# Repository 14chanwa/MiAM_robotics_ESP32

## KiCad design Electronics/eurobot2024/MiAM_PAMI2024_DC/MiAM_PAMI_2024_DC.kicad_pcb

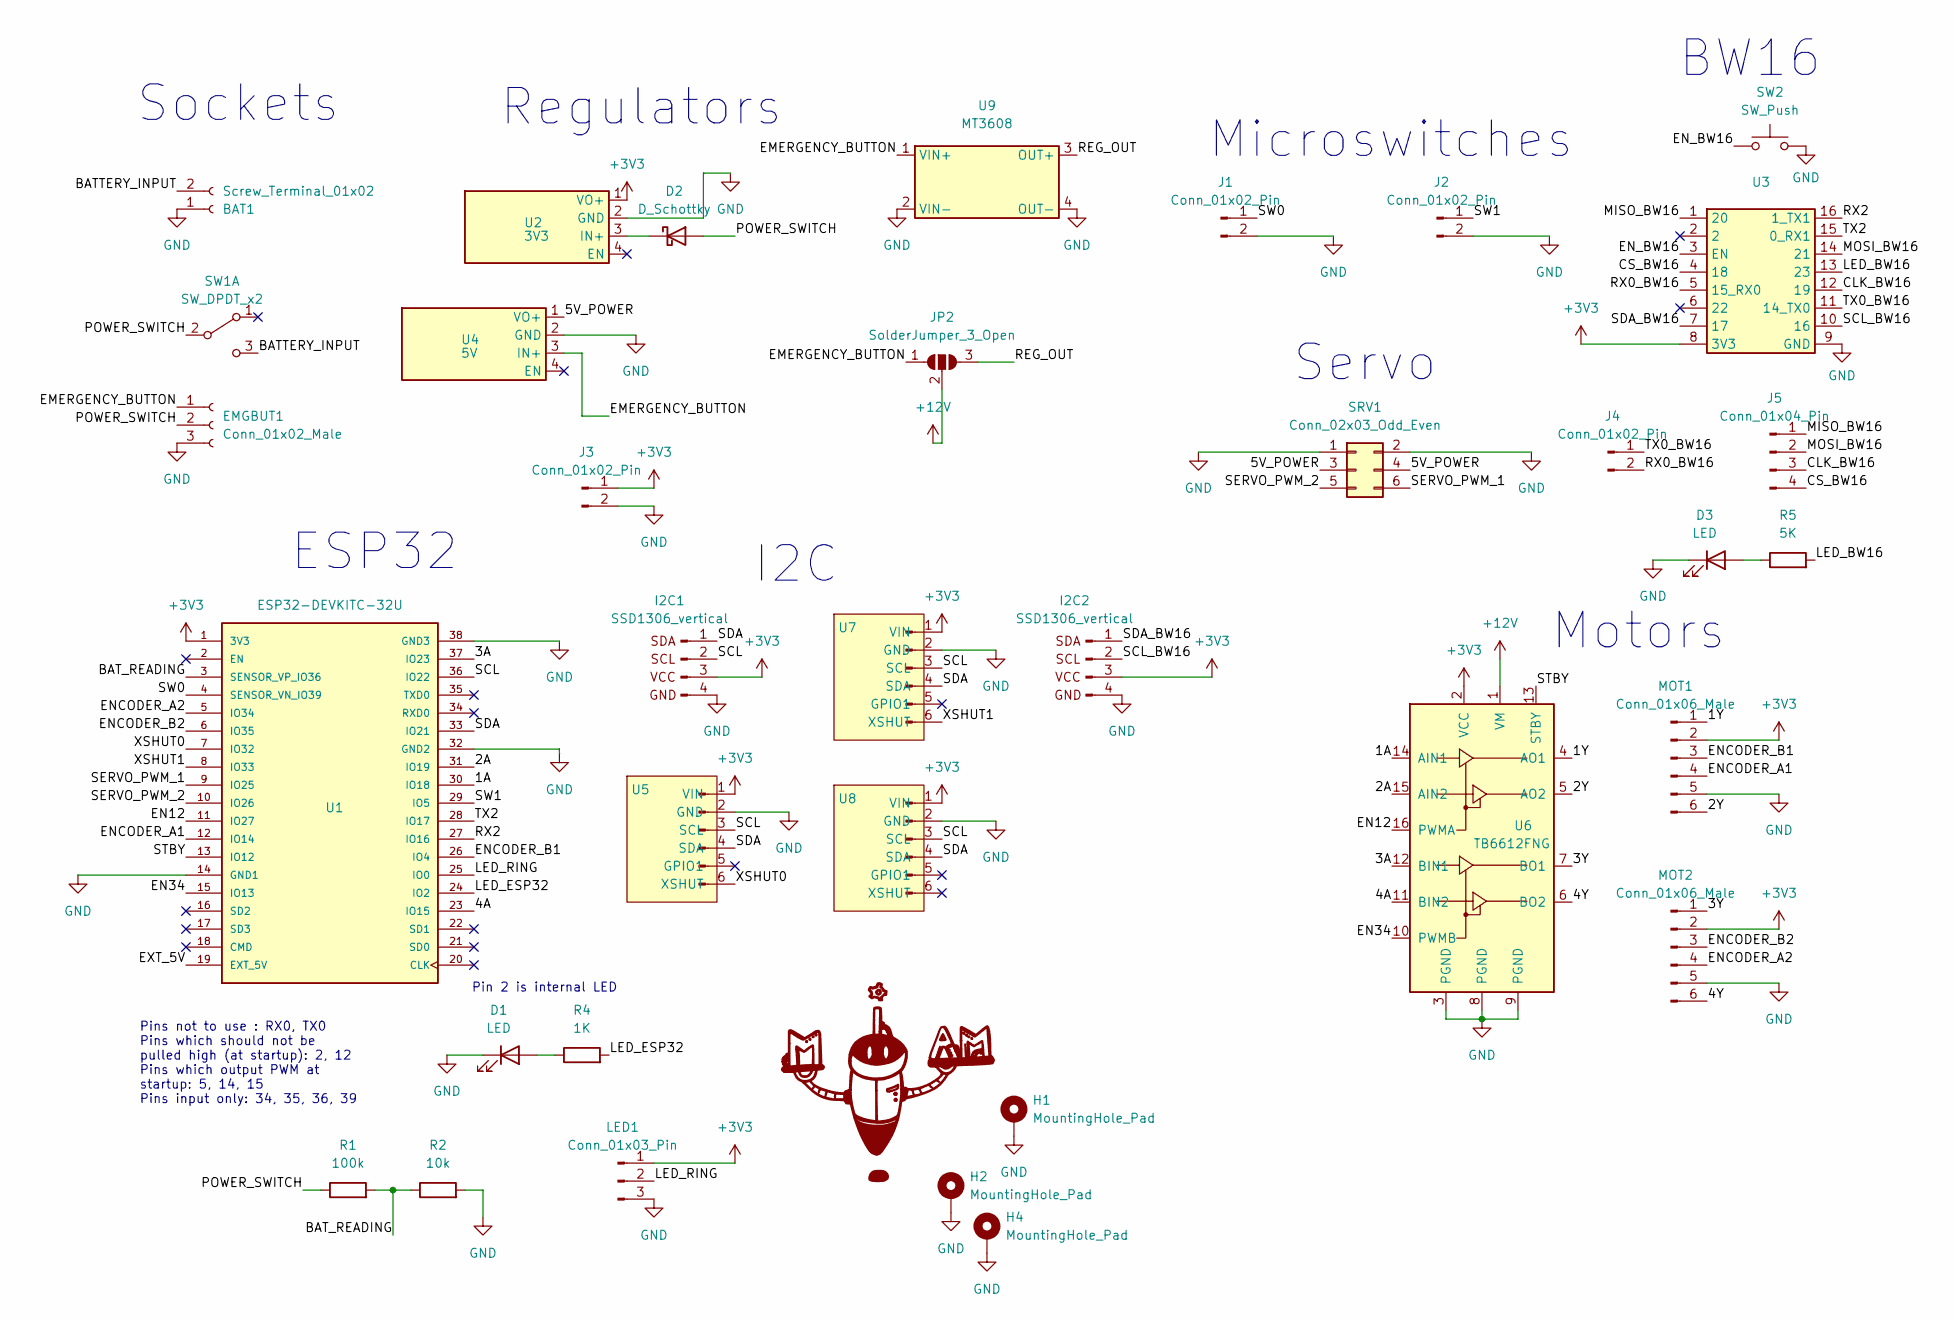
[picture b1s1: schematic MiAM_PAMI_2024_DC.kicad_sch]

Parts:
BAT1: Screw_Terminal_01x02; JST_PH_B2B-PH-K_1x02_P2.00mm_Vertical
D1, D3: LED; LED_0805_2012Metric
D2: D_Schottky; D_SOD-323_HandSoldering
EMGBUT1: Conn_01x02_Male; JST_PH_B3B-PH-K_1x03_P2.00mm_Vertical
H1, H2, H4: MountingHole_Pad; MountingHole_3.2mm_M3_DIN965_Pad
I2C1, I2C2: SSD1306_vertical; PinHeader_1x04_P2.54mm_Vertical
J1, J2, J3, J4: Conn_01x02_Pin; PinHeader_1x02_P2.54mm_Vertical
J5: Conn_01x04_Pin; PinHeader_1x04_P2.54mm_Vertical
JP2: SolderJumper_3_Open; SolderJumper-3_P1.3mm_Bridged12_Pad1.0x1.5mm_NumberLabels
LED1: Conn_01x03_Pin; PinHeader_1x03_P2.54mm_Vertical
MOT1, MOT2: Conn_01x06_Male; PinHeader_1x06_P2.54mm_Vertical
R1: 100k; R_0805_2012Metric_Pad1.20x1.40mm_HandSolder
R2: 10k; R_0805_2012Metric_Pad1.20x1.40mm_HandSolder
R4: 1K; R_0805_2012Metric
R5: 5K; R_0805_2012Metric
SRV1: Conn_02x03_Odd_Even; PinHeader_2x03_P2.54mm_Vertical
SW1: SW_DPDT_x2; SS-12D11
SW2: SW_Push; SW_Push_1P1T_NO_Vertical_Wuerth_434133025816
U1: ESP32-DEVKITC-32U; ESP32U-ShieldPattern
U2: 3V3; VoltageRegulator
U3: BW16_Breakout
U4: 5V; VoltageRegulator
U5, U7, U8: PinHeader_1x06_P2.54mm_Vertical
U6: TB6612FNG
U9: MT3608

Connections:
+3V3: I2C1.3 (VCC), I2C2.3 (VCC), J3.1, LED1.1, MOT1.2, MOT2.2, U1.1 (3V3), U2.1 (VO+), U3.8 (3V3), U5.1 (VIN), U6.2 (VCC), U7.1 (VIN), U8.1 (VIN)
+12V: JP2.2 (C), U6.1 (VM)
/1A: U1.30 (IO18), U6.14 (AIN1)
/1Y: MOT1.1, U6.4 (AO1)
/2A: U1.31 (IO19), U6.15 (AIN2)
/2Y: MOT1.6, U6.5 (AO2)
/3A: U1.37 (IO23), U6.12 (BIN1)
/3Y: MOT2.1, U6.7 (BO1)
/4A: U1.23 (IO15), U6.11 (BIN2)
/4Y: MOT2.6, U6.6 (BO2)
/5V_POWER: SRV1.3, SRV1.4, U4.1 (VO+)
/BATTERY_INPUT: BAT1.2, SW1.3 (C)
/BAT_READING: R1.2, R2.1, U1.3 (SENSOR_VP_IO36)
/CLK_BW16: J5.3, U3.12 (19)
/CS_BW16: J5.4, U3.4 (18)
/EMERGENCY_BUTTON: EMGBUT1.1, JP2.1 (A), U4.3 (IN+), U9.1 (VIN+)
/EN12: U1.11 (IO27), U6.16 (PWMA)
/EN34: U1.15 (IO13), U6.10 (PWMB)
/ENCODER_A1: MOT1.4, U1.12 (IO14)
/ENCODER_A2: MOT2.4, U1.5 (IO34)
/ENCODER_B1: MOT1.3, U1.26 (IO4)
/ENCODER_B2: MOT2.3, U1.6 (IO35)
/EN_BW16: SW2.1, U3.3 (EN)
/EXT_5V: U1.19 (EXT_5V)
/LED_BW16: R5.2, U3.13 (23)
/LED_ESP32: R4.2, U1.24 (IO2)
/LED_RING: LED1.2, U1.25 (IO0)
/MISO_BW16: J5.1, U3.1 (20)
/MOSI_BW16: J5.2, U3.14 (21)
/POWER_SWITCH: D2.2 (A), EMGBUT1.2, R1.1, SW1.2 (B)
/REG_OUT: JP2.3 (B), U9.3 (OUT+)
/RX0_BW16: J4.2, U3.5 (15_RX0)
/RX2: U1.27 (IO16), U3.16 (1_TX1)
/SCL: I2C1.2 (SCL), U1.36 (IO22), U5.3 (SCL), U7.3 (SCL), U8.3 (SCL)
/SCL_BW16: I2C2.2 (SCL), U3.10 (16)
/SDA: I2C1.1 (SDA), U1.33 (IO21), U5.4 (SDA), U7.4 (SDA), U8.4 (SDA)
/SDA_BW16: I2C2.1 (SDA), U3.7 (17)
/SERVO_PWM_1: SRV1.6, U1.9 (IO25)
/SERVO_PWM_2: SRV1.5, U1.10 (IO26)
/STBY: U1.13 (IO12), U6.13 (STBY)
/SW0: J1.1, U1.4 (SENSOR_VN_IO39)
/SW1: J2.1, U1.29 (IO5)
/TX0_BW16: J4.1, U3.11 (14_TX0)
/TX2: U1.28 (IO17), U3.15 (0_RX1)
/XSHUT0: U1.7 (IO32), U5.6 (XSHUT)
/XSHUT1: U1.8 (IO33), U7.6 (XSHUT)
GND: BAT1.1, D1.1 (K), D3.1 (K), EMGBUT1.3, H1.1, H2.1, H4.1, I2C1.4 (GND), I2C2.4 (GND), J1.2, J2.2, J3.2, LED1.3, MOT1.5, MOT2.5, R2.2, SRV1.1, SRV1.2, SW2.2, U1.14 (GND1), U1.32 (GND2), U1.38 (GND3), U2.2 (GND), U3.9 (GND), U4.2 (GND), U5.2 (GND), U6.3 (PGND), U6.8 (PGND), U6.9 (PGND), U7.2 (GND), U8.2 (GND), U9.2 (VIN-), U9.4 (OUT-)
unnamed: D1.2 (A), R4.1
unnamed: D2.1 (K), U2.3 (IN+)
unnamed: D3.2 (A), R5.1

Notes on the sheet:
Pins not to use : RX0, TX0 Pins which should not be pulled high (at startup): 2, 12 Pins which output PWM at startup: 5, 14, 15 Pins input only: 34, 35, 36, 39
Sockets
ESP32
Regulators
BW16
Microswitches
Pin 2 is internal LED
I2C
Motors
Servo

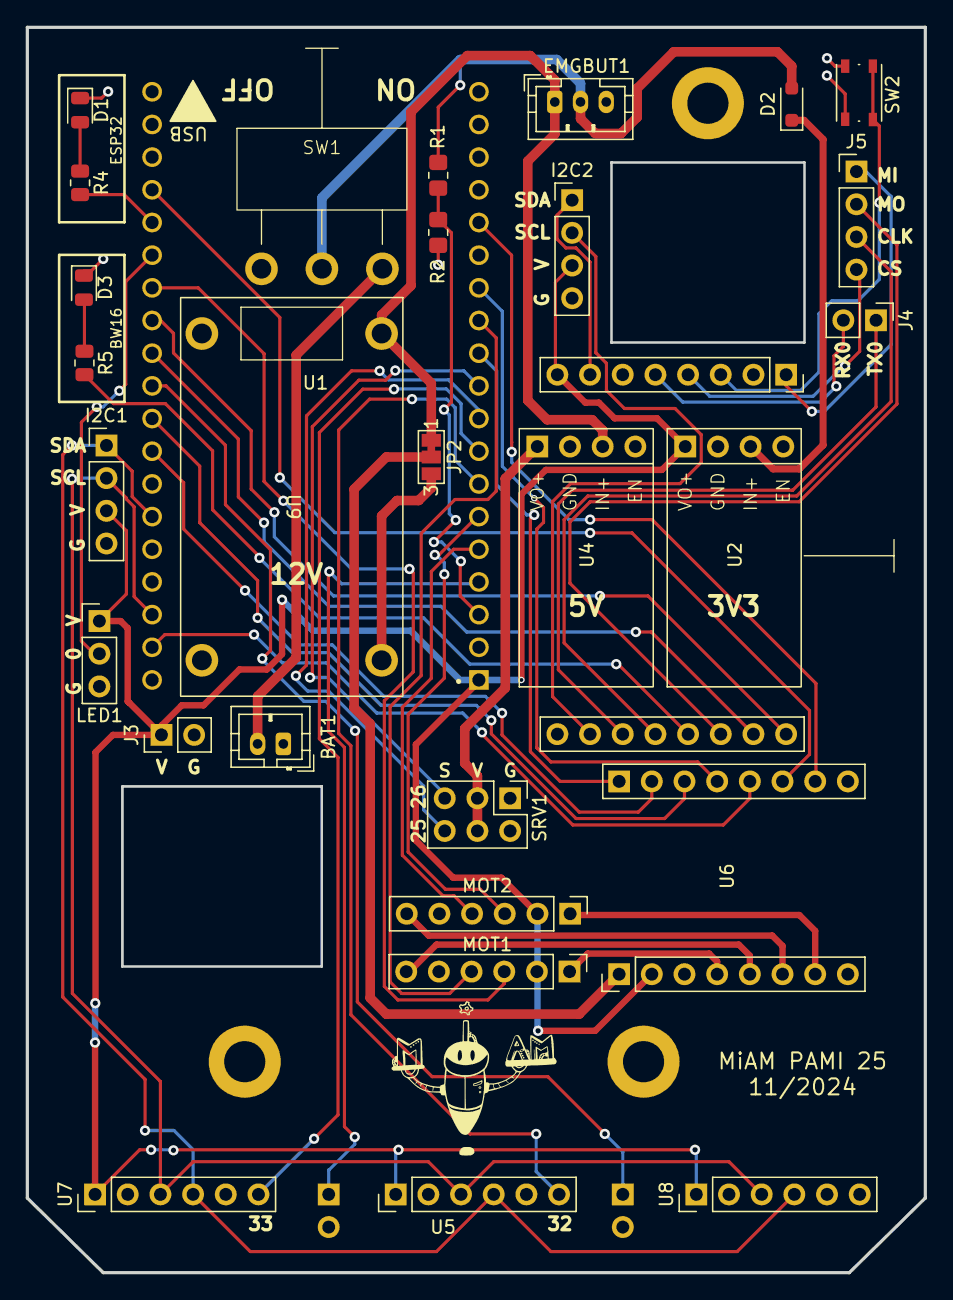
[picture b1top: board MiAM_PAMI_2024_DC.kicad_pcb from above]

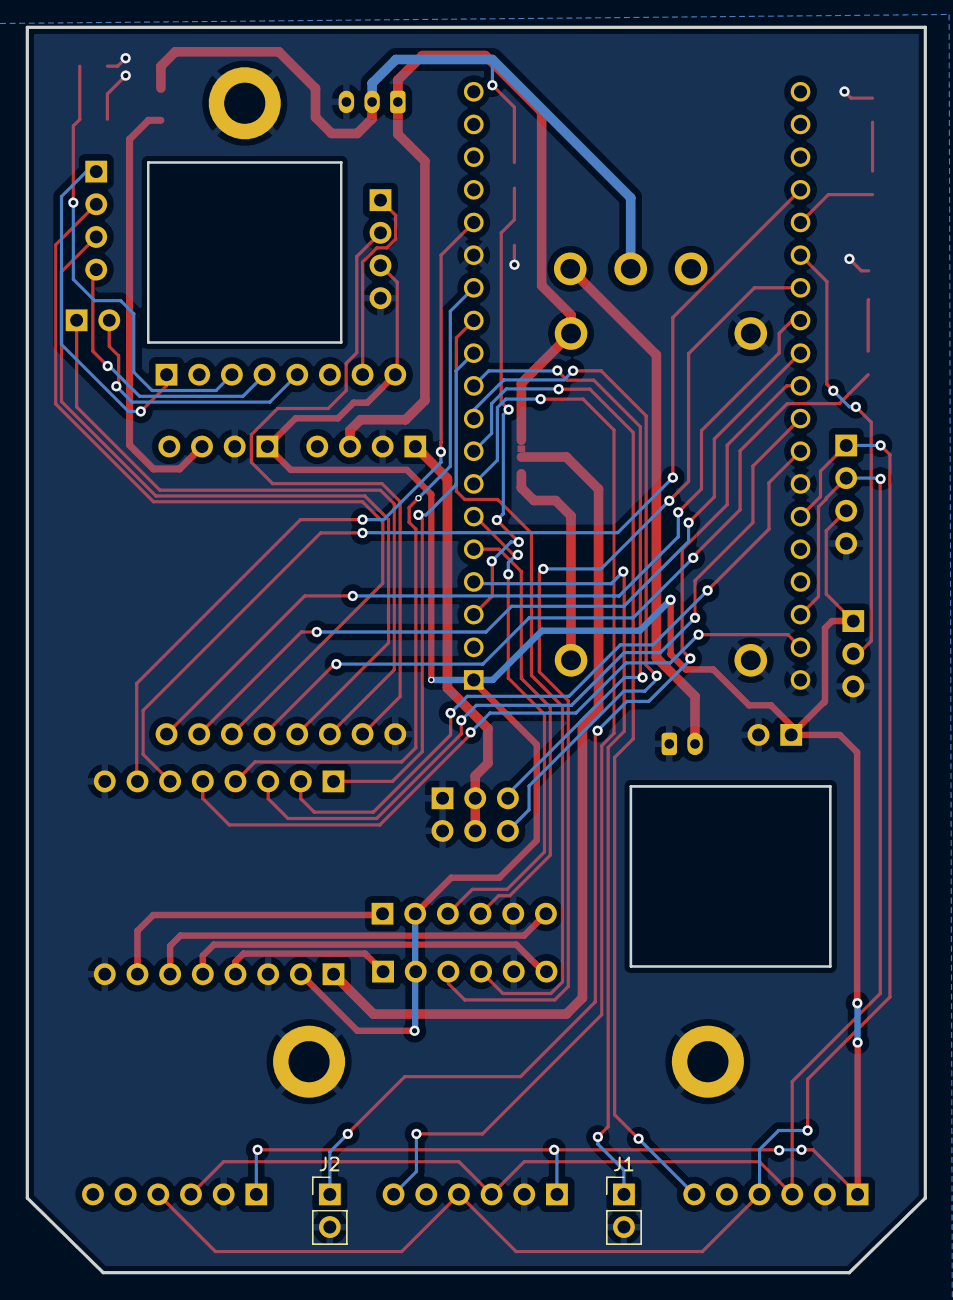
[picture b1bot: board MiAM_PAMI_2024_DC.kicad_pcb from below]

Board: 2 copper layers, 69.8 x 96.8 mm, 35 parts (2 on the bottom side), 49 nets.

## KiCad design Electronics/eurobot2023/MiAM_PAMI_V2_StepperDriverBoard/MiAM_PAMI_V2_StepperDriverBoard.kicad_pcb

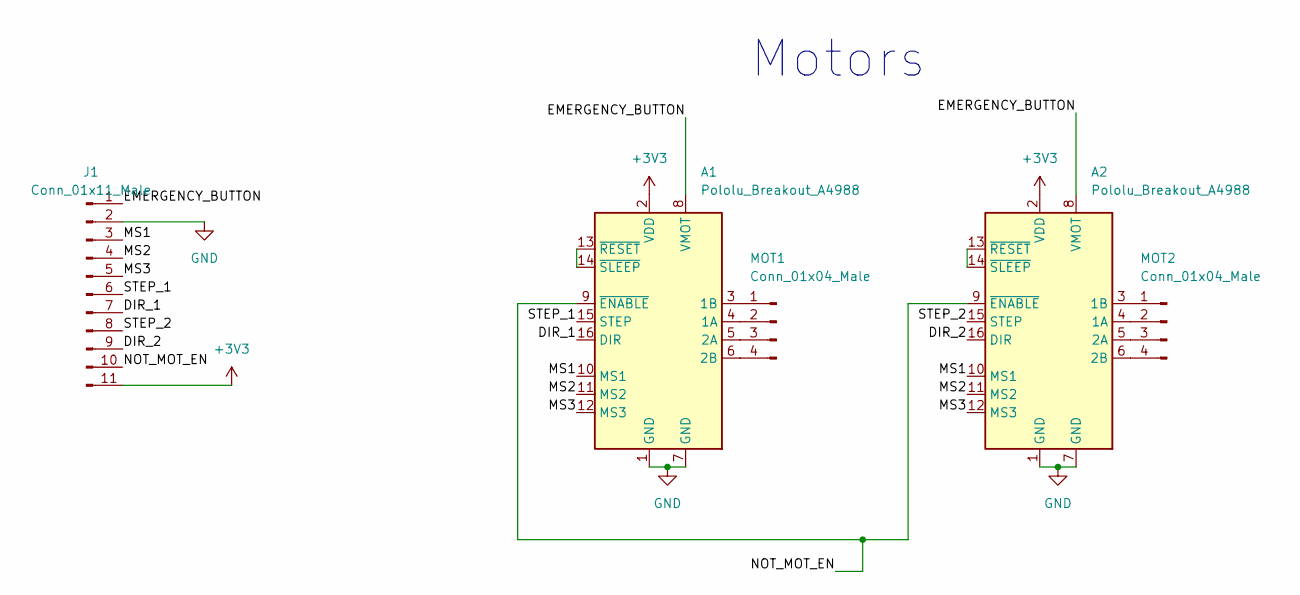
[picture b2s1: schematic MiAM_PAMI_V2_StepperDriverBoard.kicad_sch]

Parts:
A1, A2: Pololu_Breakout_A4988; Pololu_Breakout-16_15.2x20.3mm
J1: Conn_01x11_Male; PinSocket_1x11_P2.54mm_Vertical
MOT1, MOT2: Conn_01x04_Male; PinHeader_1x04_P2.54mm_Vertical

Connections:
+3V3: A1.2 (VDD), A2.2 (VDD), J1.11
/DIR_1: A1.16 (DIR), J1.7
/DIR_2: A2.16 (DIR), J1.9
/EMERGENCY_BUTTON: A1.8 (VMOT), A2.8 (VMOT), J1.1
/MS1: A1.10 (MS1), A2.10 (MS1), J1.3
/MS2: A1.11 (MS2), A2.11 (MS2), J1.4
/MS3: A1.12 (MS3), A2.12 (MS3), J1.5
/NOT_MOT_EN: A1.9 (~ENABLE), A2.9 (~ENABLE), J1.10
/STEP_1: A1.15 (STEP), J1.6
/STEP_2: A2.15 (STEP), J1.8
GND: A1.1 (GND), A1.7 (GND), A2.1 (GND), A2.7 (GND), J1.2
unnamed: A1.4 (1A), MOT1.2
unnamed: A1.3 (1B), MOT1.1
unnamed: A1.5 (2A), MOT1.3
unnamed: A1.6 (2B), MOT1.4
unnamed: A1.13 (~RESET), A1.14 (~SLEEP)
unnamed: A2.4 (1A), MOT2.2
unnamed: A2.3 (1B), MOT2.1
unnamed: A2.5 (2A), MOT2.3
unnamed: A2.6 (2B), MOT2.4
unnamed: A2.13 (~RESET), A2.14 (~SLEEP)

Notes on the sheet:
Motors

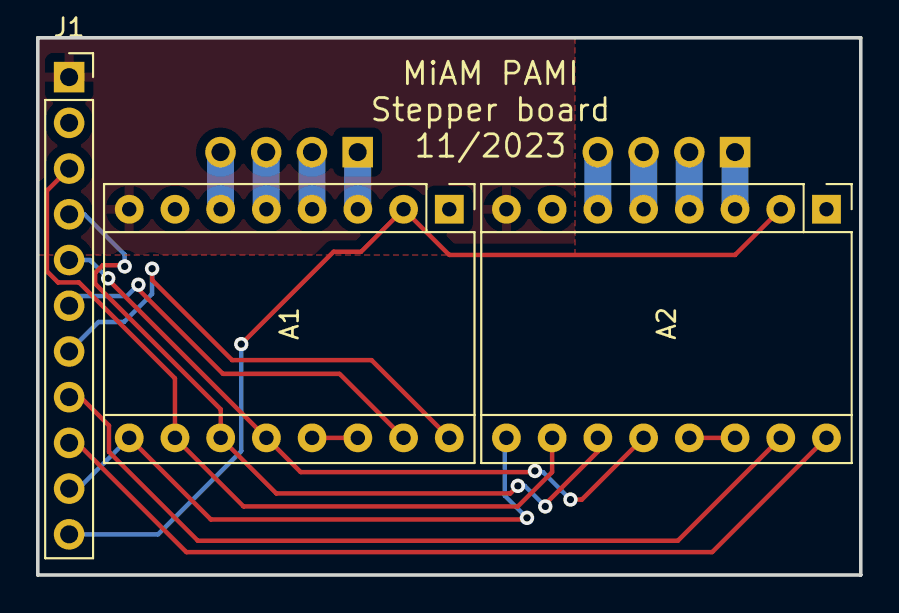
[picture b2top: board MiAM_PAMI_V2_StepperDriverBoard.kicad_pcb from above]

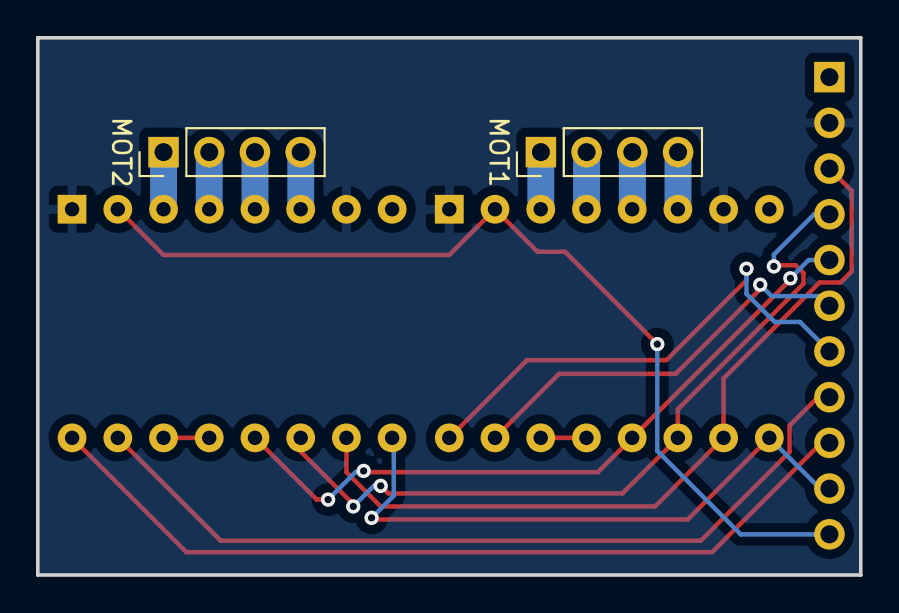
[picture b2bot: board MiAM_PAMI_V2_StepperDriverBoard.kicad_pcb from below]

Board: 2 copper layers, 45.7 x 29.8 mm, 5 parts (2 on the bottom side), 21 nets.

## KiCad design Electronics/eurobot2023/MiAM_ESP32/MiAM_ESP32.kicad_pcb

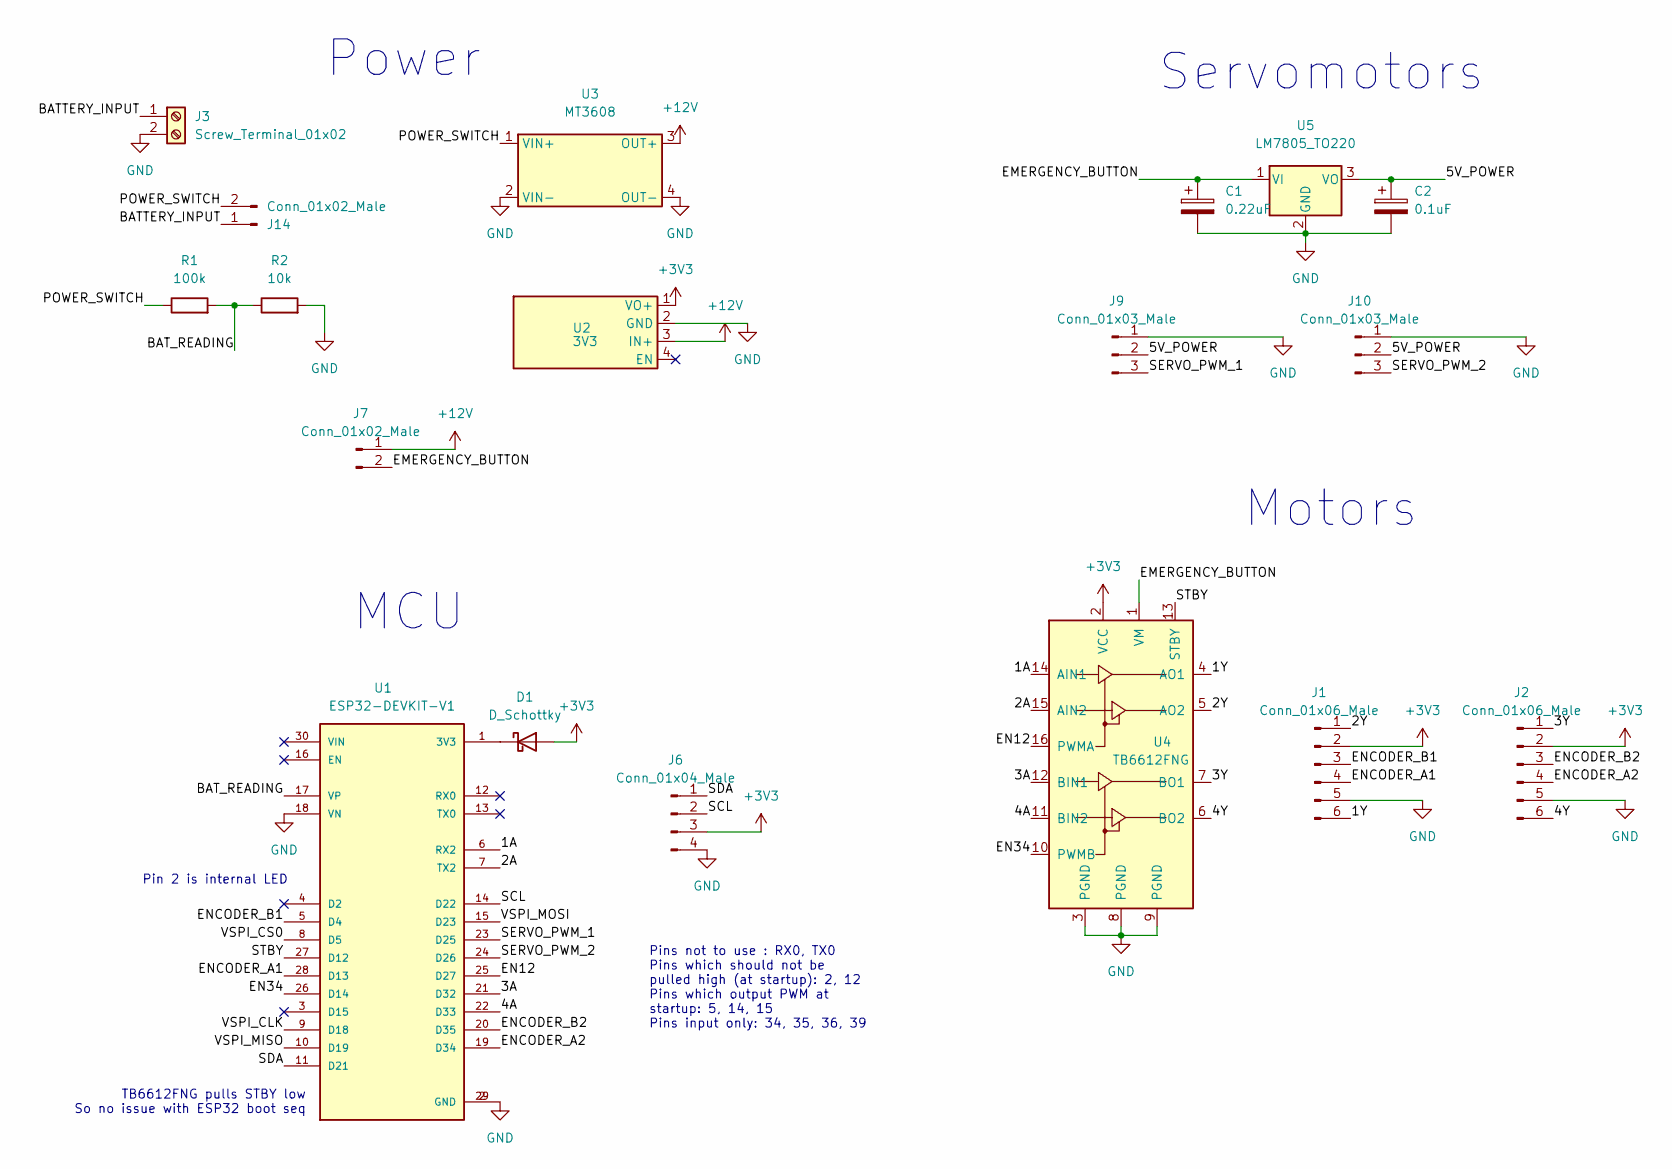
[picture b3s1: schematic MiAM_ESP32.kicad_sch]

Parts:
C1: 0.22uF; CP_Radial_D4.0mm_P2.00mm
C2: 0.1uF; CP_Radial_Tantal_D5.0mm_P5.00mm
D1: D_Schottky; D_DO-41_SOD81_P7.62mm_Horizontal
J1, J2: Conn_01x06_Male; PinHeader_1x06_P2.54mm_Vertical
J3: Screw_Terminal_01x02; JST_PH_B2B-PH-K_1x02_P2.00mm_Vertical
J6: Conn_01x04_Male; PinHeader_1x04_P2.54mm_Vertical
J7, J14: Conn_01x02_Male; PinHeader_1x02_P2.54mm_Vertical
J9, J10: Conn_01x03_Male; PinHeader_1x03_P2.54mm_Vertical
R1: 100k; R_Axial_DIN0309_L9.0mm_D3.2mm_P12.70mm_Horizontal
R2: 10k; R_Axial_DIN0309_L9.0mm_D3.2mm_P12.70mm_Horizontal
U1: ESP32-DEVKIT-V1; MODULE_ESP32_DEVKIT_V1; PARTREV N/A
U2: 3V3; VoltageRegulator
U3: MT3608
U4: TB6612FNG
U5: LM7805_TO220; TO-220-3_Vertical

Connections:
+3V3: D1.2 (A), J1.2, J2.2, J6.3, U2.1 (VO+), U4.2 (VCC)
+12V: J7.1, U2.3 (IN+), U3.3 (OUT+)
/1A: U1.6 (RX2), U4.14 (AIN1)
/1Y: J1.6, U4.4 (AO1)
/2A: U1.7 (TX2), U4.15 (AIN2)
/2Y: J1.1, U4.5 (AO2)
/3A: U1.21 (D32), U4.12 (BIN1)
/3Y: J2.1, U4.7 (BO1)
/4A: U1.22 (D33), U4.11 (BIN2)
/4Y: J2.6, U4.6 (BO2)
/5V_POWER: C2.1, J9.2, J10.2, U5.3 (VO)
/BATTERY_INPUT: J3.1, J14.1
/BAT_READING: R1.2, R2.1, U1.17 (VP)
/EMERGENCY_BUTTON: C1.1, J7.2, U4.1 (VM), U5.1 (VI)
/EN12: U1.25 (D27), U4.16 (PWMA)
/EN34: U1.26 (D14), U4.10 (PWMB)
/ENCODER_A1: J1.4, U1.28 (D13)
/ENCODER_A2: J2.4, U1.19 (D34)
/ENCODER_B1: J1.3, U1.5 (D4)
/ENCODER_B2: J2.3, U1.20 (D35)
/POWER_SWITCH: J14.2, R1.1, U3.1 (VIN+)
/SCL: J6.2, U1.14 (D22)
/SDA: J6.1, U1.11 (D21)
/SERVO_PWM_1: J9.3, U1.23 (D25)
/SERVO_PWM_2: J10.3, U1.24 (D26)
/STBY: U1.27 (D12), U4.13 (STBY)
/VSPI_CLK: U1.9 (D18)
/VSPI_CS0: U1.8 (D5)
/VSPI_MISO: U1.10 (D19)
/VSPI_MOSI: U1.15 (D23)
GND: C1.2, C2.2, J1.5, J2.5, J3.2, J6.4, J9.1, J10.1, R2.2, U1.2 (GND), U1.18 (VN), U1.29 (GND), U2.2 (GND), U3.2 (VIN-), U3.4 (OUT-), U4.3 (PGND), U4.8 (PGND), U4.9 (PGND), U5.2 (GND)
unnamed: D1.1 (K), U1.1 (3V3)

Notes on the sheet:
Servomotors
Pin 2 is internal LED
Power
TB6612FNG pulls STBY low So no issue with ESP32 boot seq
MCU
Motors
Pins not to use : RX0, TX0 Pins which should not be pulled high (at startup): 2, 12 Pins which output PWM at startup: 5, 14, 15 Pins input only: 34, 35, 36, 39

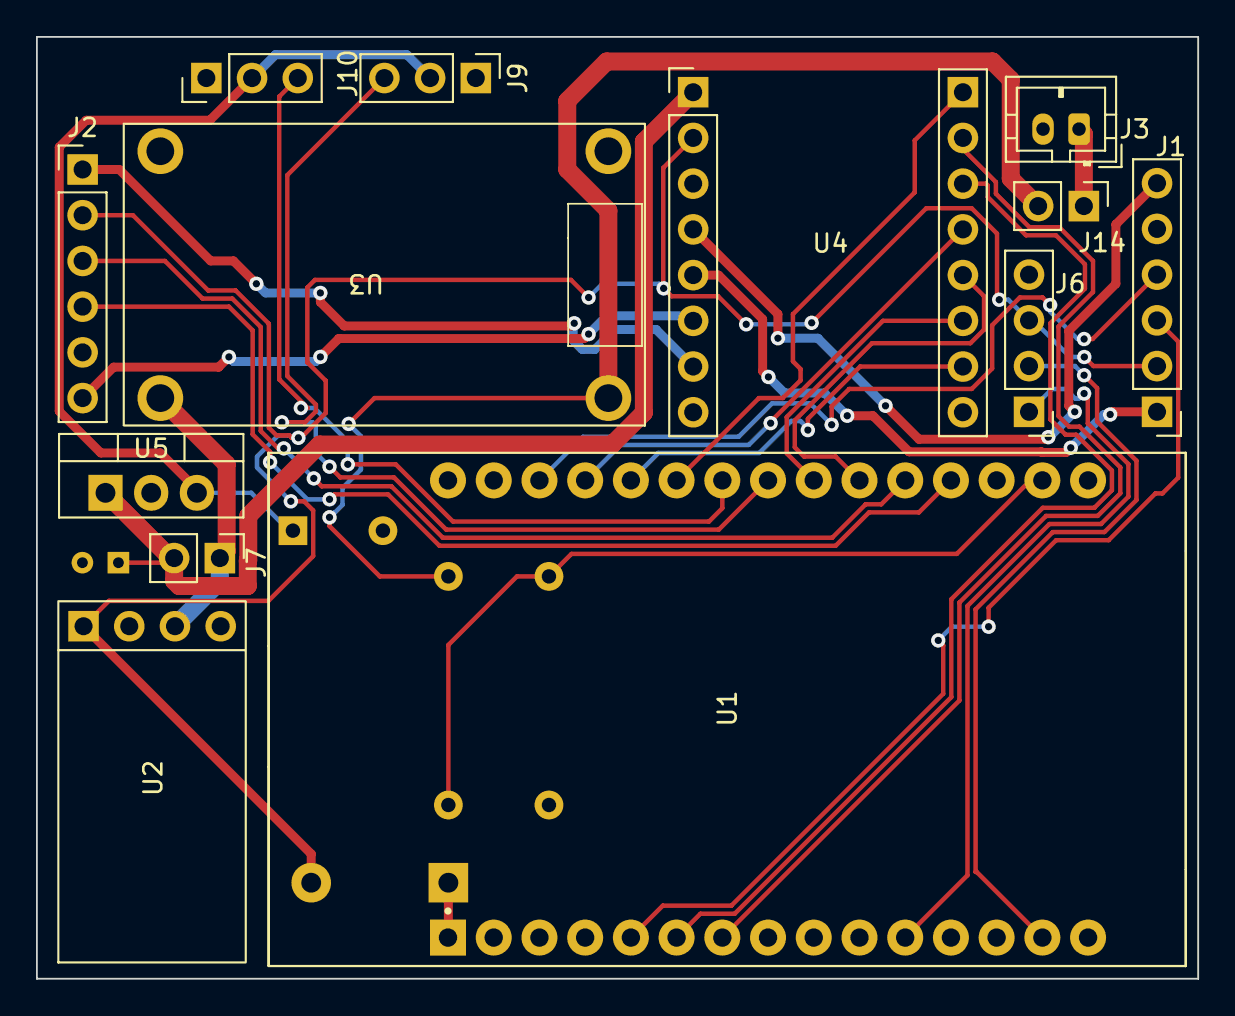
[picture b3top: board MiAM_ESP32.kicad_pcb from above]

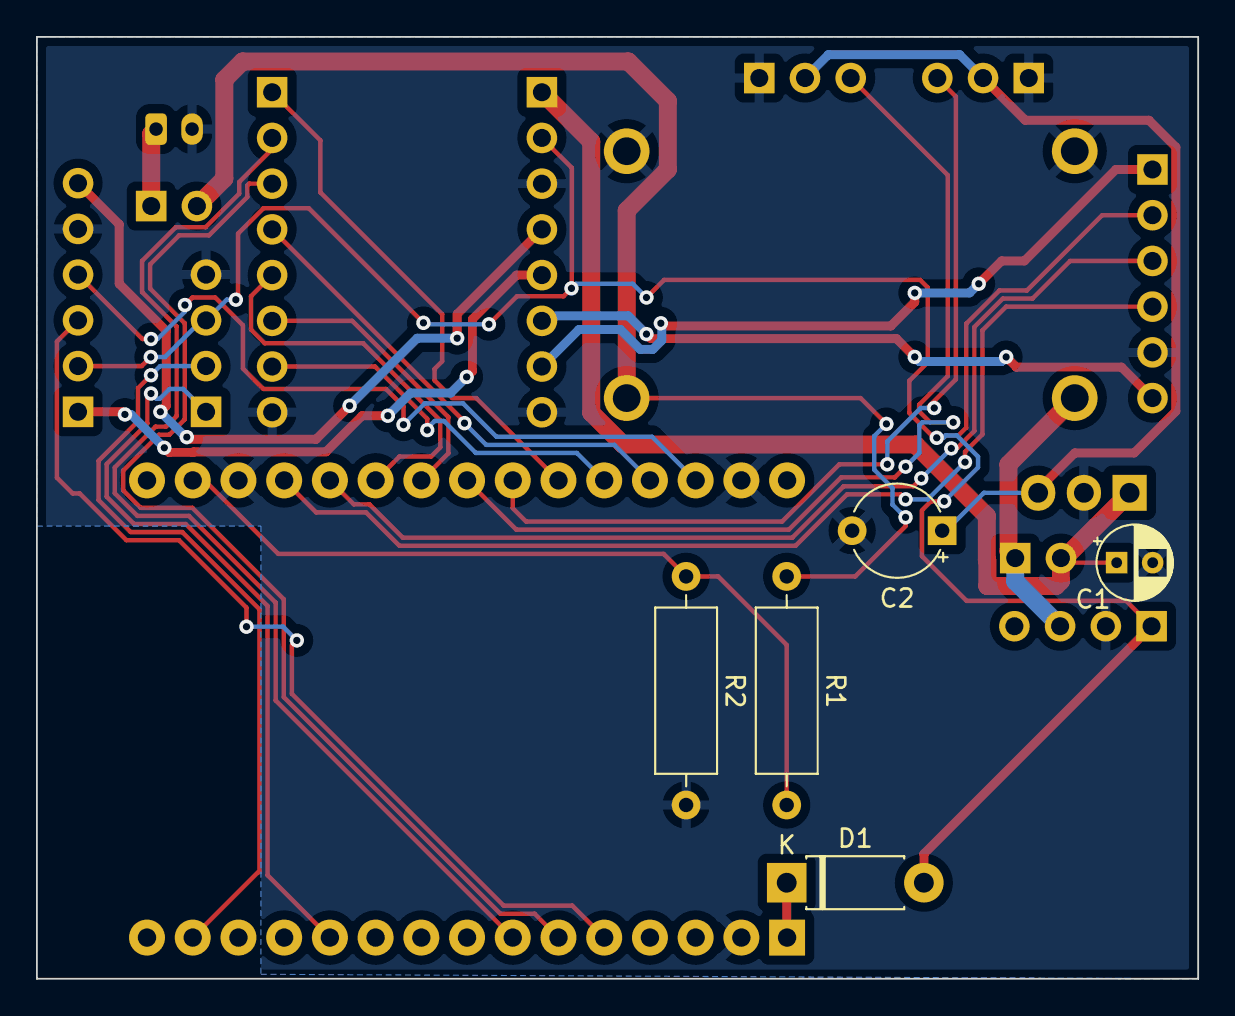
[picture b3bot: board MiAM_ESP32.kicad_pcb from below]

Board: 2 copper layers, 64.5 x 52.3 mm, 18 parts (5 on the bottom side), 28 nets.

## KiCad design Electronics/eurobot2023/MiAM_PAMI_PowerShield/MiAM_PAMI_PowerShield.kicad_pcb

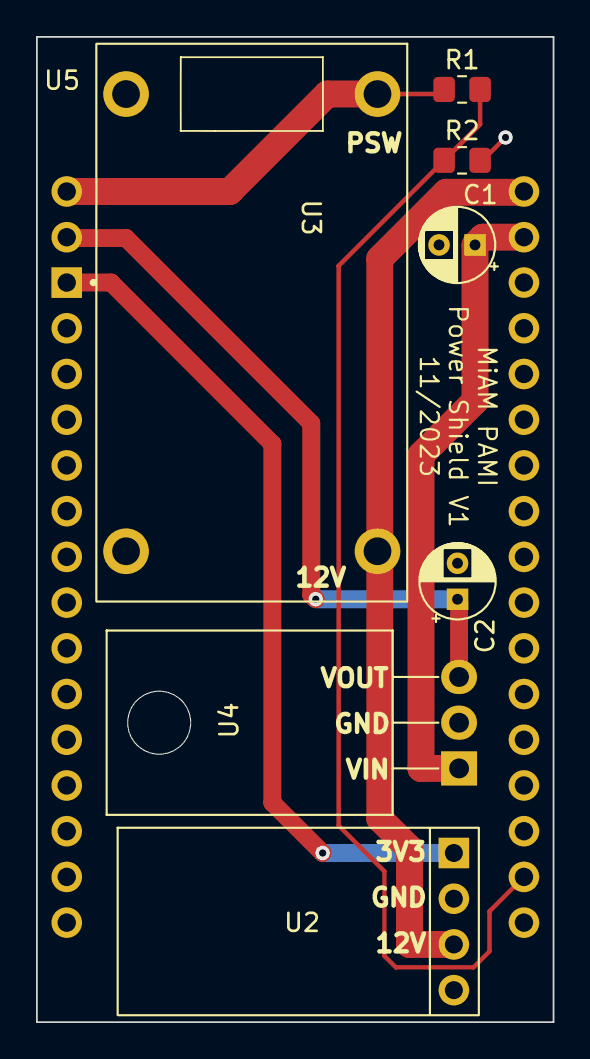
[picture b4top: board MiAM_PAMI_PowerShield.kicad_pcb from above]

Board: 2 copper layers, 28.7 x 54.7 mm, 8 parts (0 on the bottom side), 7 nets.

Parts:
C1: 0.22uF; CP_Radial_D4.0mm_P2.00mm
C2: 0.1uF; CP_Radial_D4.0mm_P2.00mm
R1: 100k; R_0805_2012Metric_Pad1.20x1.40mm_HandSolder
R2: 10k; R_0805_2012Metric_Pad1.20x1.40mm_HandSolder
U2: 3V3; VoltageRegulator
U3: MT3608
U4: LM7805_TO220; TO-220-3_Horizontal_TabDown
U5: ESP32-DEVKIT-V1; ESP32_ShieldPattern

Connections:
+3V3: U2.1 (VO+), U5.1 (3V3)
+12V: U2.3 (IN+), U3.3 (OUT+), U5.SH2 (12V)
/5V_POWER: C2.1, U4.3 (VO), U5.SH3 (SERVO_V)
/BAT_READING: R1.2, R2.1, U5.17 (VP)
/EMERGENCY_BUTTON: C1.1, U4.1 (VI), U5.SH1 (EMG_BUT)
/POWER_SWITCH: R1.1, U3.1 (VIN+), U5.SH4 (POW_SW)
GND: C1.2, C2.2, R2.2, U2.2 (GND), U3.2 (VIN-), U3.4 (OUT-), U4.2 (GND), U5.18 (VN), U5.29 (GND)

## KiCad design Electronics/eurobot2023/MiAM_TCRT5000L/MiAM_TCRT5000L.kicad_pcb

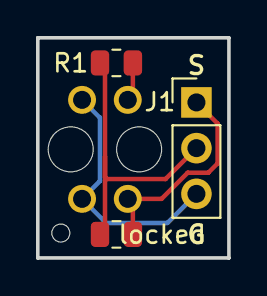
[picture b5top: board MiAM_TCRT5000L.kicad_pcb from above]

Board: 2 copper layers, 10.6 x 12.2 mm, 4 parts (1 on the bottom side), 4 nets.

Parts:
IC1: TCRT5000L
J1: Conn_01x03_Pin; PinHeader_1x03_P2.54mm_Vertical
R1: 100; R_0805_2012Metric
locked: 5000; R_0805_2012Metric

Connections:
+3V3: J1.2, R1.1, locked.1
/S: IC1.1 (COLLECTOR), J1.1, locked.2
GND: IC1.2 (EMITTER), IC1.3 (CATHODE), J1.3
unnamed: IC1.4 (ANODE), R1.2

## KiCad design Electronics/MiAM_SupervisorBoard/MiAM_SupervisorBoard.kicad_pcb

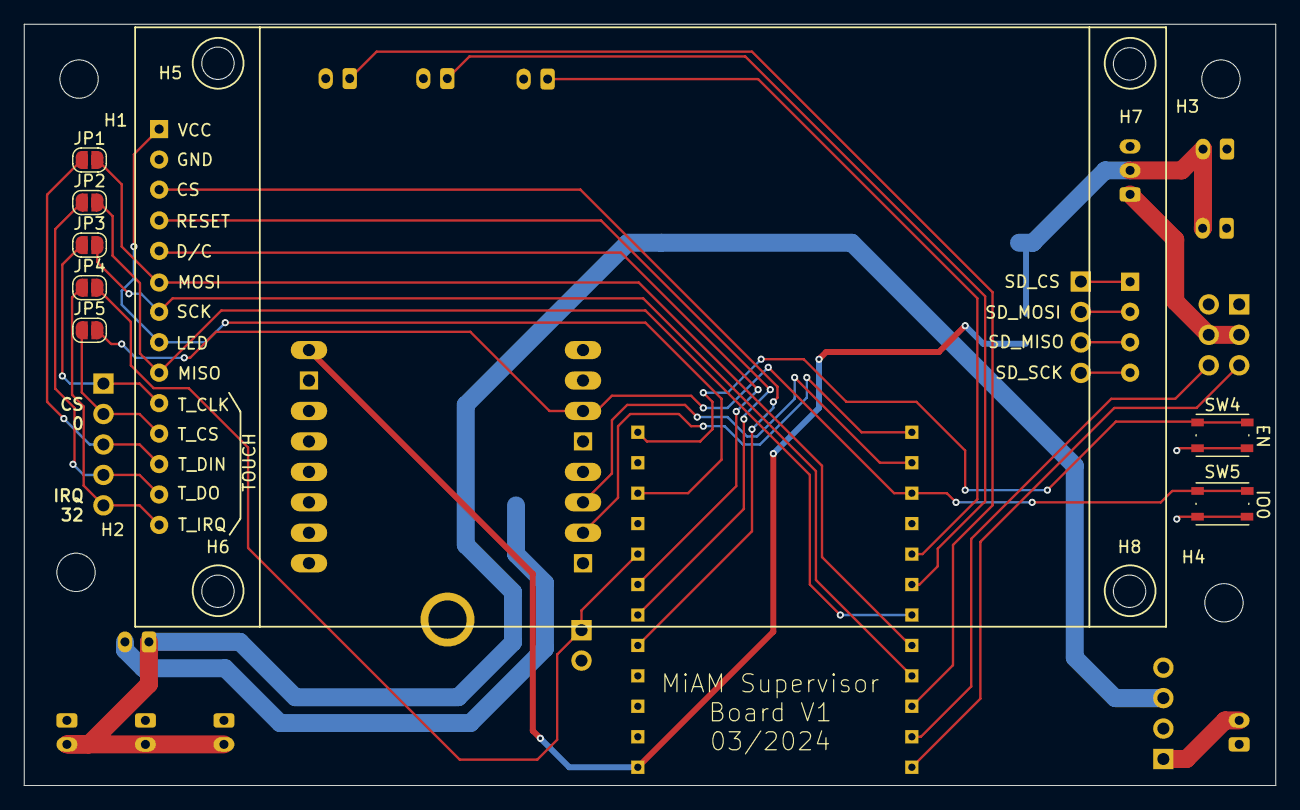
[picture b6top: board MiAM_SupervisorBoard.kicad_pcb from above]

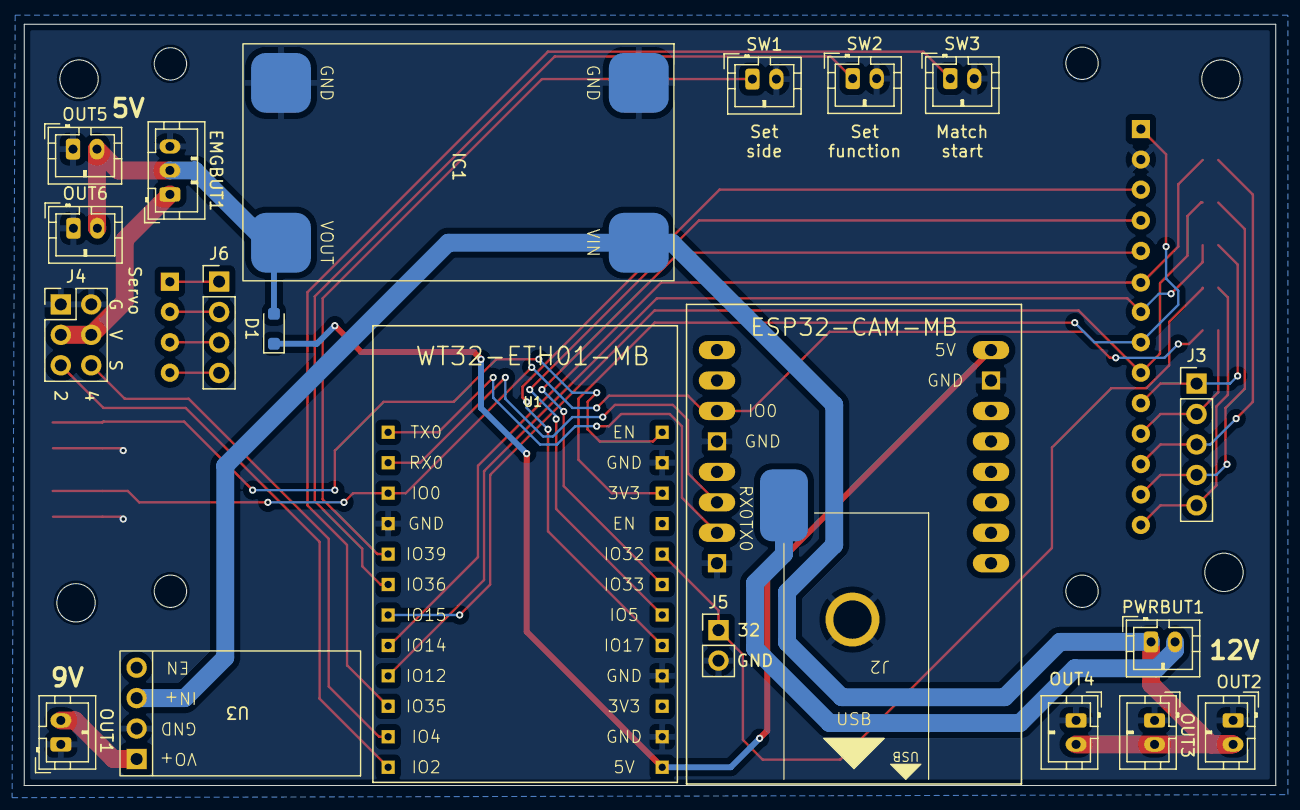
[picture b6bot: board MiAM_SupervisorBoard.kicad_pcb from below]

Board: 2 copper layers, 104.4 x 63.5 mm, 37 parts (21 on the bottom side), 33 nets.

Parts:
D1: D_Schottky; D_SOD-323_HandSoldering
EMGBUT1: Conn_01x02_Male; JST_PH_B3B-PH-K_1x03_P2.00mm_Vertical
H1, H2, H3, H4: MountingHole; MountingHole_3.2mm_M3
H5, H6, H7, H8: MountingHole; MountingHole_2.7mm_M2.5
IC1: Mini560
J1: ST7789_TFT_Screen; 2.8_tft_240x320_touch_sd_spi
J2: Screw_Terminal_01x02; USBC-Dummy-Card
J3: Conn_01x05_Pin; PinHeader_1x05_P2.54mm_Vertical
J4: Conn_02x03_Odd_Even; PinHeader_2x03_P2.54mm_Vertical
J5: Conn_01x02_Pin; PinHeader_1x02_P2.54mm_Vertical
J6: Conn_01x04_Pin; PinHeader_1x04_P2.54mm_Vertical
JP1, JP2, JP3, JP4, JP5: SolderJumper_2_Open; SolderJumper-2_P1.3mm_Open_RoundedPad1.0x1.5mm
OUT1, OUT2, OUT3, OUT4, OUT5, OUT6: Screw_Terminal_01x02; JST_PH_B2B-PH-K_1x02_P2.00mm_Vertical
PWRBUT1: Screw_Terminal_01x02; JST_PH_B2B-PH-K_1x02_P2.00mm_Vertical
SW1, SW2, SW3: SW_Push; JST_PH_B2B-PH-K_1x02_P2.00mm_Vertical
SW4, SW5: SW_Push; SW_Push_1P1T_NO_Vertical_Wuerth_434133025816
U1: WT32-ETH01; WT32-ETH01-MB
U2: ESP32-CAM; ESP32-CAM_MB
U3: 9V; VoltageRegulator

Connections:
+3V3: J1.1 (VCC), J1.8 (LED), U1.3V3
+5V: D1.2 (A), EMGBUT1.2, IC1.2 (VOUT), OUT5.2, OUT6.2
+5VA: D1.1 (K), U1.5V, U2.P$9 (5V)
+9V: OUT1.2, U3.1 (VO+)
+12V: IC1.3 (VIN), OUT2.2, OUT3.2, OUT4.2, PWRBUT1.1, U3.3 (IN+)
/CS: J1.3 (CS), U1.TXD
/DC: J1.5 (DC), U1.485_EN
/EMERGENCY_BUTTON: EMGBUT1.1, J4.3, J4.4
/EN: SW4.1, U1.EN
/IO0: JP5.2 (B), SW5.1, U1.IO0, U2.P$6 (GPIO0)
/IO2: J4.5, U1.IO2
/IO4: J4.6, U1.IO4
/IO32: J5.1, JP4.2 (B), U1.CFG
/MATCH_START: SW3.1, U1.IO35
/MISO: J1.9 (MISO), JP2.2 (B), U1.IO15
/MOSI: J1.6 (MOSI), JP1.2 (B), U1.IO14
/RESET: J1.4 (RESET), U1.RXD
/RX0: U1.RX0, U2.P$3 (GPIO3)
/SCK: J1.7 (SCK), JP3.2 (B), U1.IO12
/SET_OTHER_FUNCTION: SW2.1, U1.IO36
/SET_SIDE: SW1.1, U1.IO39
/TX0: U1.TX0, U2.P$2 (GPIO1)
/T_CLK: J1.10 (T_CLK), J3.1, JP3.1 (A)
/T_CS: J1.11 (T_CS), J3.2, JP5.1 (A)
/T_DIN: J1.12 (T_DIN), J3.3, JP1.1 (A)
/T_DO: J1.13 (T_DO), J3.4, JP2.1 (A)
/T_IRQ: J1.14 (T_IRQ), J3.5, JP4.1 (A)
GND: EMGBUT1.3, IC1.1 (GND), IC1.4 (GND), J1.2 (GND), J2.2, J4.1, J4.2, J5.2, OUT1.1, OUT2.1, OUT3.1, OUT4.1, OUT5.1, OUT6.1, SW1.2, SW2.2, SW3.2, SW4.2, SW5.2, U1.GND, U1.GND@1, U1.GND@2, U1.GND@3, U2.P$1 (GND@1), U2.P$5 (GND@2), U2.P$10 (GND@3), U3.2 (GND)
unnamed: J1.15 (SD_CS), J6.1
unnamed: J1.17 (SD_MISO), J6.3
unnamed: J1.16 (SD_MOSI), J6.2
unnamed: J1.18 (SD_SCK), J6.4
unnamed: J2.1, PWRBUT1.2
